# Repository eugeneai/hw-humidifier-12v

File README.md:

# hw-humidifier-12v
A Humidifier for Auto with 12v power supply.

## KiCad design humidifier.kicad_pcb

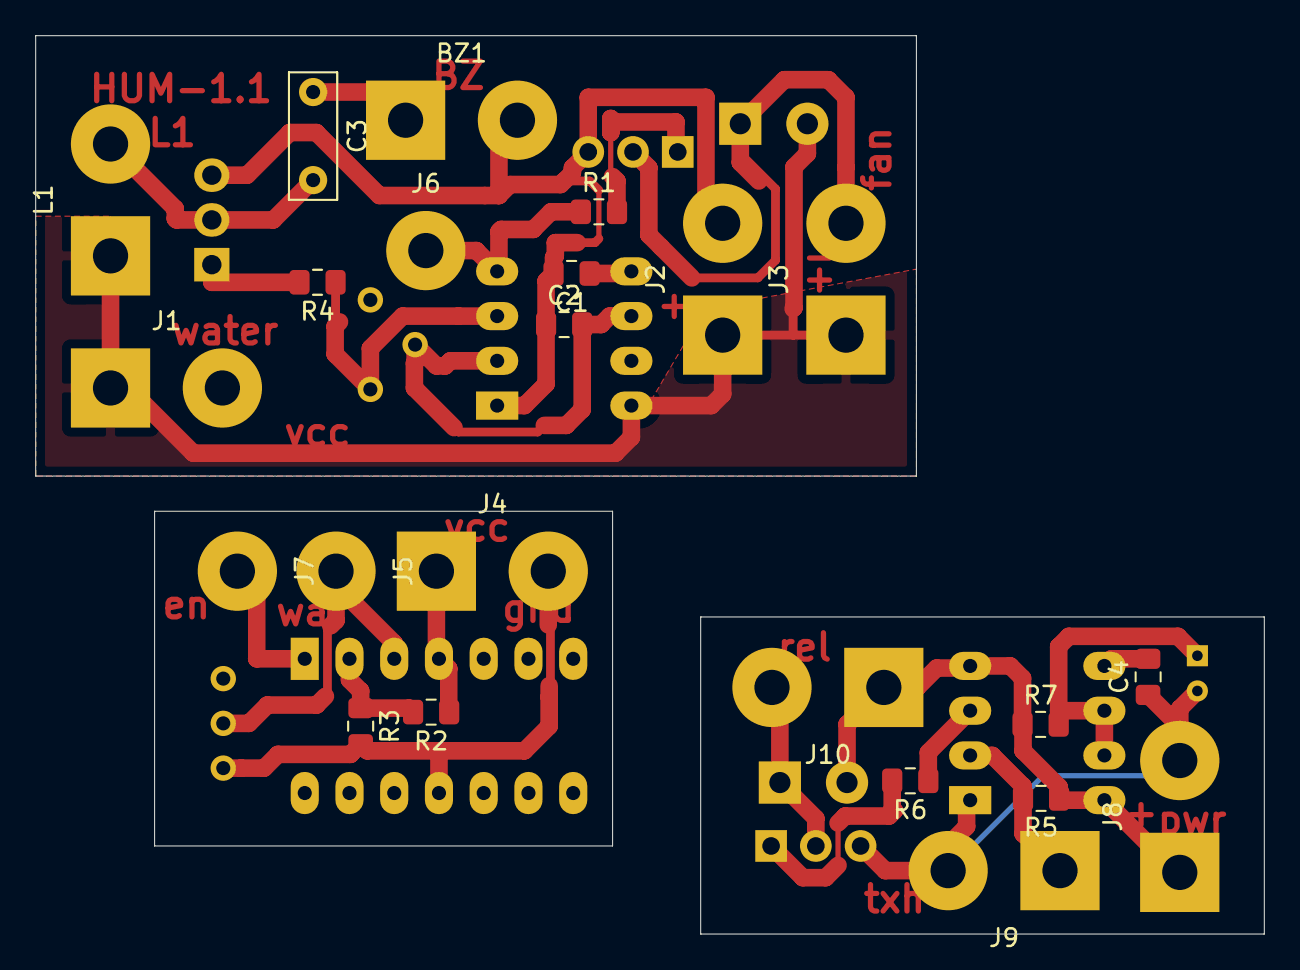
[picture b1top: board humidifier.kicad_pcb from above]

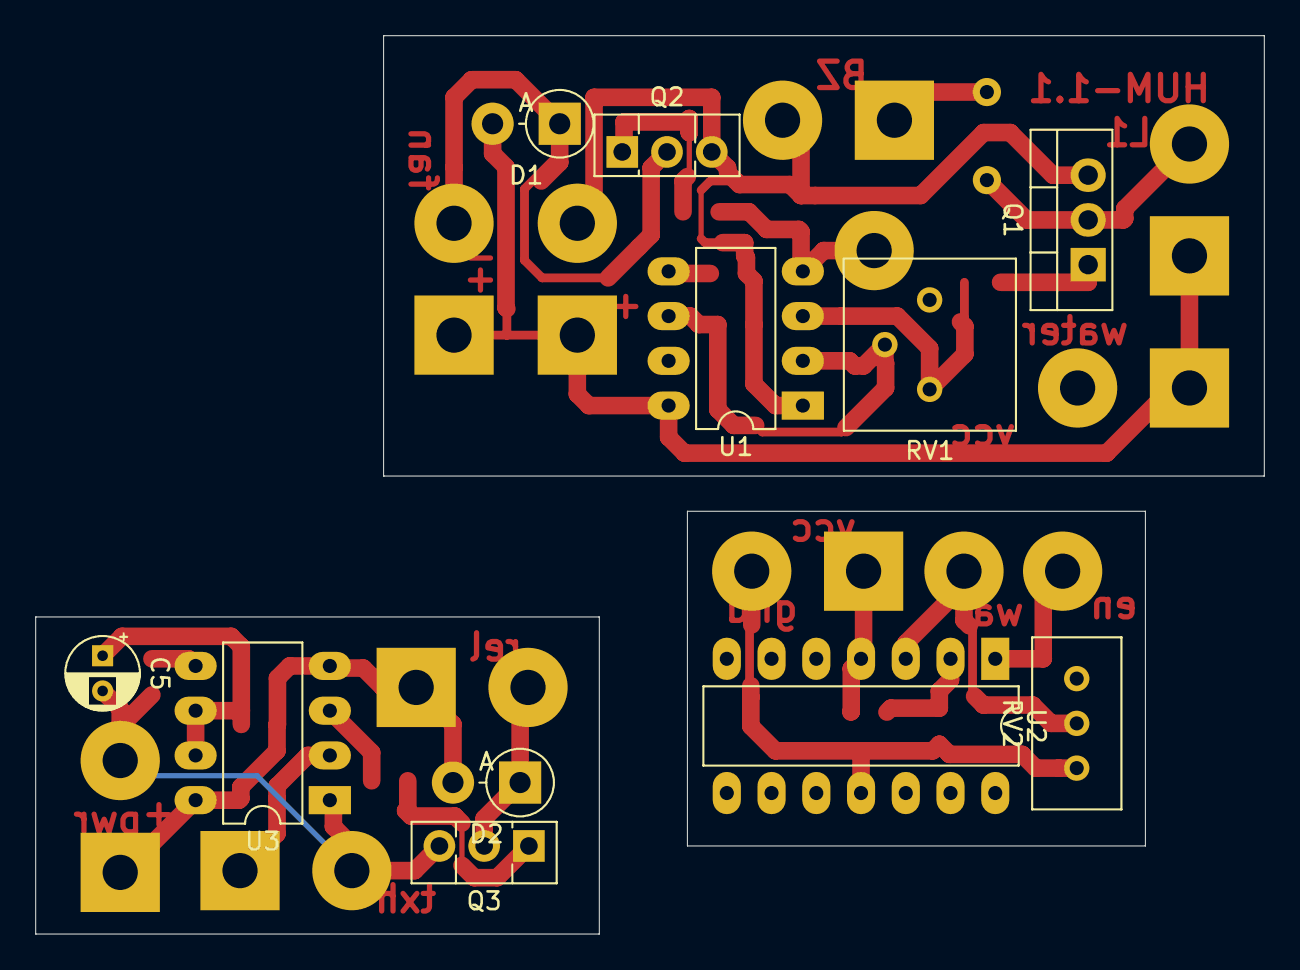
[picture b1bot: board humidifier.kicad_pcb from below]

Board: 2 copper layers, 69.8 x 51.0 mm, 34 parts (11 on the bottom side), 19 nets.

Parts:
BZ1: Buzzer; SolderWirePad_1x02_P7.62mm_Drill2mm
C1, C4: 100n; C_0805_2012Metric_Pad1.15x1.40mm_HandSolder
C2: 10n; C_0805_2012Metric_Pad1.15x1.40mm_HandSolder
C3: 100nF; C_Disc_D7.0mm_W2.5mm_P5.00mm
C5: 10u; CP_Radial_D4.0mm_P2.00mm
D1, D2: 4141; D_DO-15_P3.81mm_Vertical_AnodeUp
J1: Level; SolderWirePad_1x02_P7.62mm_Drill2mm
J2, J4, J8: PWR; SolderWirePad_1x02_P7.62mm_Drill2mm
J3: FAN; SolderWirePad_1x02_P7.62mm_Drill2mm
J5: water; SolderWirePad_1x01_Drill2mm
J6, J7: en; SolderWirePad_1x01_Drill2mm
J9: THNX; SolderWirePad_1x02_P7.62mm_Drill2mm
J10: REL; SolderWirePad_1x02_P7.62mm_Drill2mm
L1: 220u; SolderWirePad_1x02_P7.62mm_Drill2mm
Q1: IRF740; TO-220-3_Vertical
Q2, Q3: MJE13003; TO-126-3_Vertical
R1, R6: 1k; R_0805_2012Metric_Pad1.15x1.40mm_HandSolder
R2: 47k; R_0805_2012Metric_Pad1.15x1.40mm_HandSolder
R3: 47K; R_0805_2012Metric_Pad1.15x1.40mm_HandSolder
R4: 10R; R_0805_2012Metric_Pad1.15x1.40mm_HandSolder
R5: 100K; R_0805_2012Metric_Pad1.15x1.40mm_HandSolder
R7: 500K; R_0805_2012Metric_Pad1.15x1.40mm_HandSolder
RV1: 5K; Potentiometer_Bourns_3386P_Vertical
RV2: 100K; Potentiometer_Bourns_3296W_Vertical
U1, U3: NE555; DIP-8_W7.62mm_LongPads
U2: LM324; DIP-14_W7.62mm_LongPads

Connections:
26: C2.2, RV1.2, U1.2, U1.6
EN: J6.1, J7.1, R1.1, U1.4, U2.1
GND: BZ1.2, C1.2, C2.1, C4.1, C5.2, J2.2, J4.2, J8.2, J9.2, Q1.3, Q2.3, Q3.3, R3.2, RV2.3, U1.1, U2.11, U3.1
unnamed: BZ1.1, C3.1
unnamed: C1.1, U1.5
unnamed: C3.2, L1.2, Q1.2
unnamed: C4.2, U3.5
unnamed: C5.1, R7.2, U3.6, U3.7
unnamed: D1.1, J3.2, Q2.2
unnamed: J9.1, R5.2, U3.2
unnamed: Q1.1, R4.2
unnamed: Q2.1, R1.2
unnamed: Q3.1, R6.2
unnamed: R2.2, R3.1, U2.2
unnamed: R4.1, RV1.3, U1.3
unnamed: R6.1, U3.3
REL: D2.1, J10.2, Q3.2
VCC: D1.2, D2.2, J1.1, J2.1, J3.1, J4.1, J8.1, J10.1, L1.1, R2.1, R5.1, R7.1, U1.8, U2.4, U3.4, U3.8
water: J1.2, J5.1, RV2.2, U2.3

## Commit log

2019-07-11 Initial import
2019-07-13 Release candidate.
2019-07-14 Added sensor based on OA lm324.
2019-07-24 Added timer.
2019-07-24 Added annotations.
2020-05-29 Renewal of components
